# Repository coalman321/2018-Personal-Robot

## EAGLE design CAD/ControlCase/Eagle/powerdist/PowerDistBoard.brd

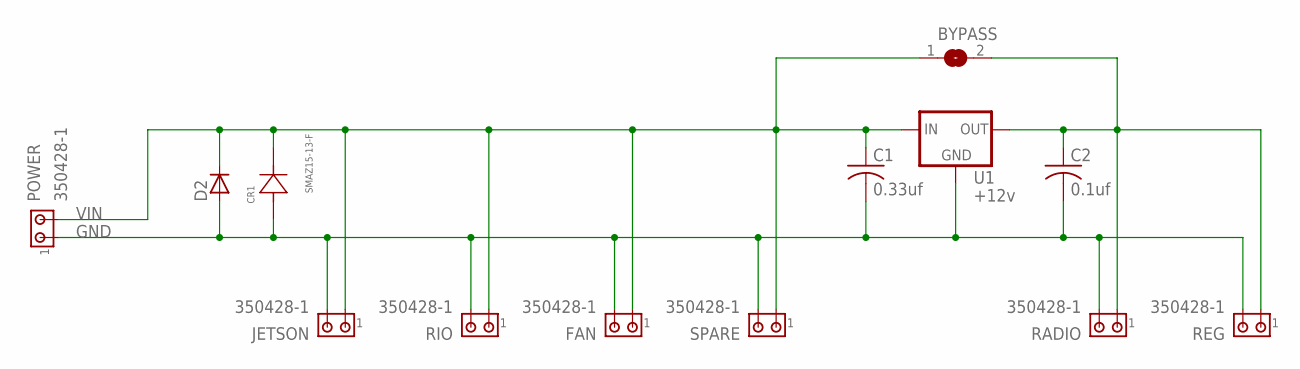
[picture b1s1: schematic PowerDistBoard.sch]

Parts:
BYPASS: SJW
C1: 0.33uf; C0603
C2: 0.1uf; C0603
CR1: SMAZ15-13-F; SMA
D2: D-SOD-80; SOD80
FAN: 350428-1
JETSON: 350428-1
POWER: 350428-1
RADIO: 350428-1
REG: 350428-1
RIO: 350428-1
SPARE: 350428-1
U1: +12v; TO-252

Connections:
GND: C1.2, C2.2, CR1.2 (21), D2.2 (A), FAN.2, JETSON.2, POWER.1, RADIO.2, REG.2, RIO.2, SPARE.2, U1.3 (GND)
unnamed: BYPASS.2, C2.1, RADIO.1, REG.1, U1.2 (OUT)
VIN: BYPASS.1, C1.1, CR1.1 (12), D2.1 (C), FAN.1, JETSON.1, POWER.2, RIO.1, SPARE.1, U1.1 (IN)

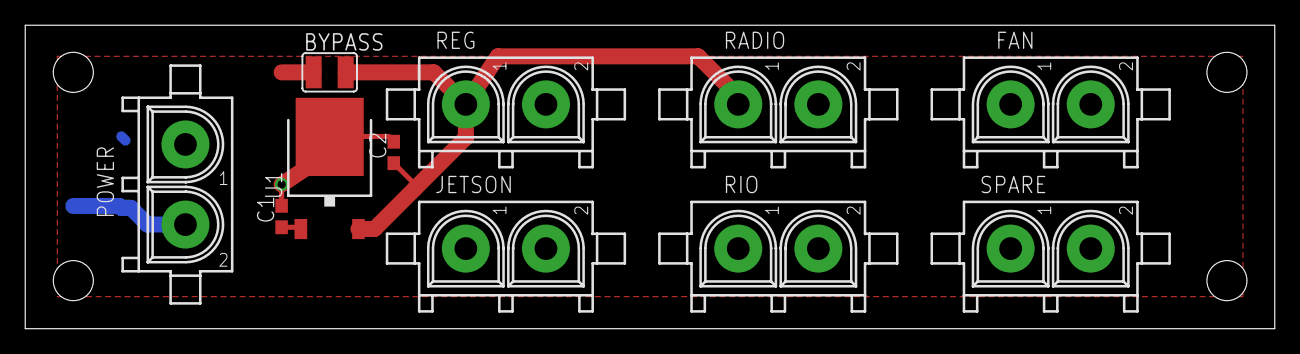
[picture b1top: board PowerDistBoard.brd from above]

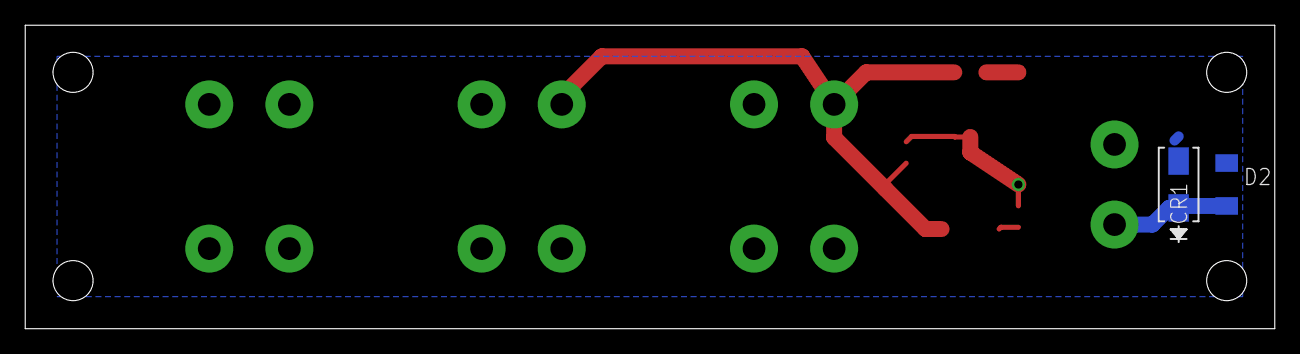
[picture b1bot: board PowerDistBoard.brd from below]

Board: 2 copper layers, 99.0 x 24.1 mm, 13 parts (2 on the bottom side), 3 nets.

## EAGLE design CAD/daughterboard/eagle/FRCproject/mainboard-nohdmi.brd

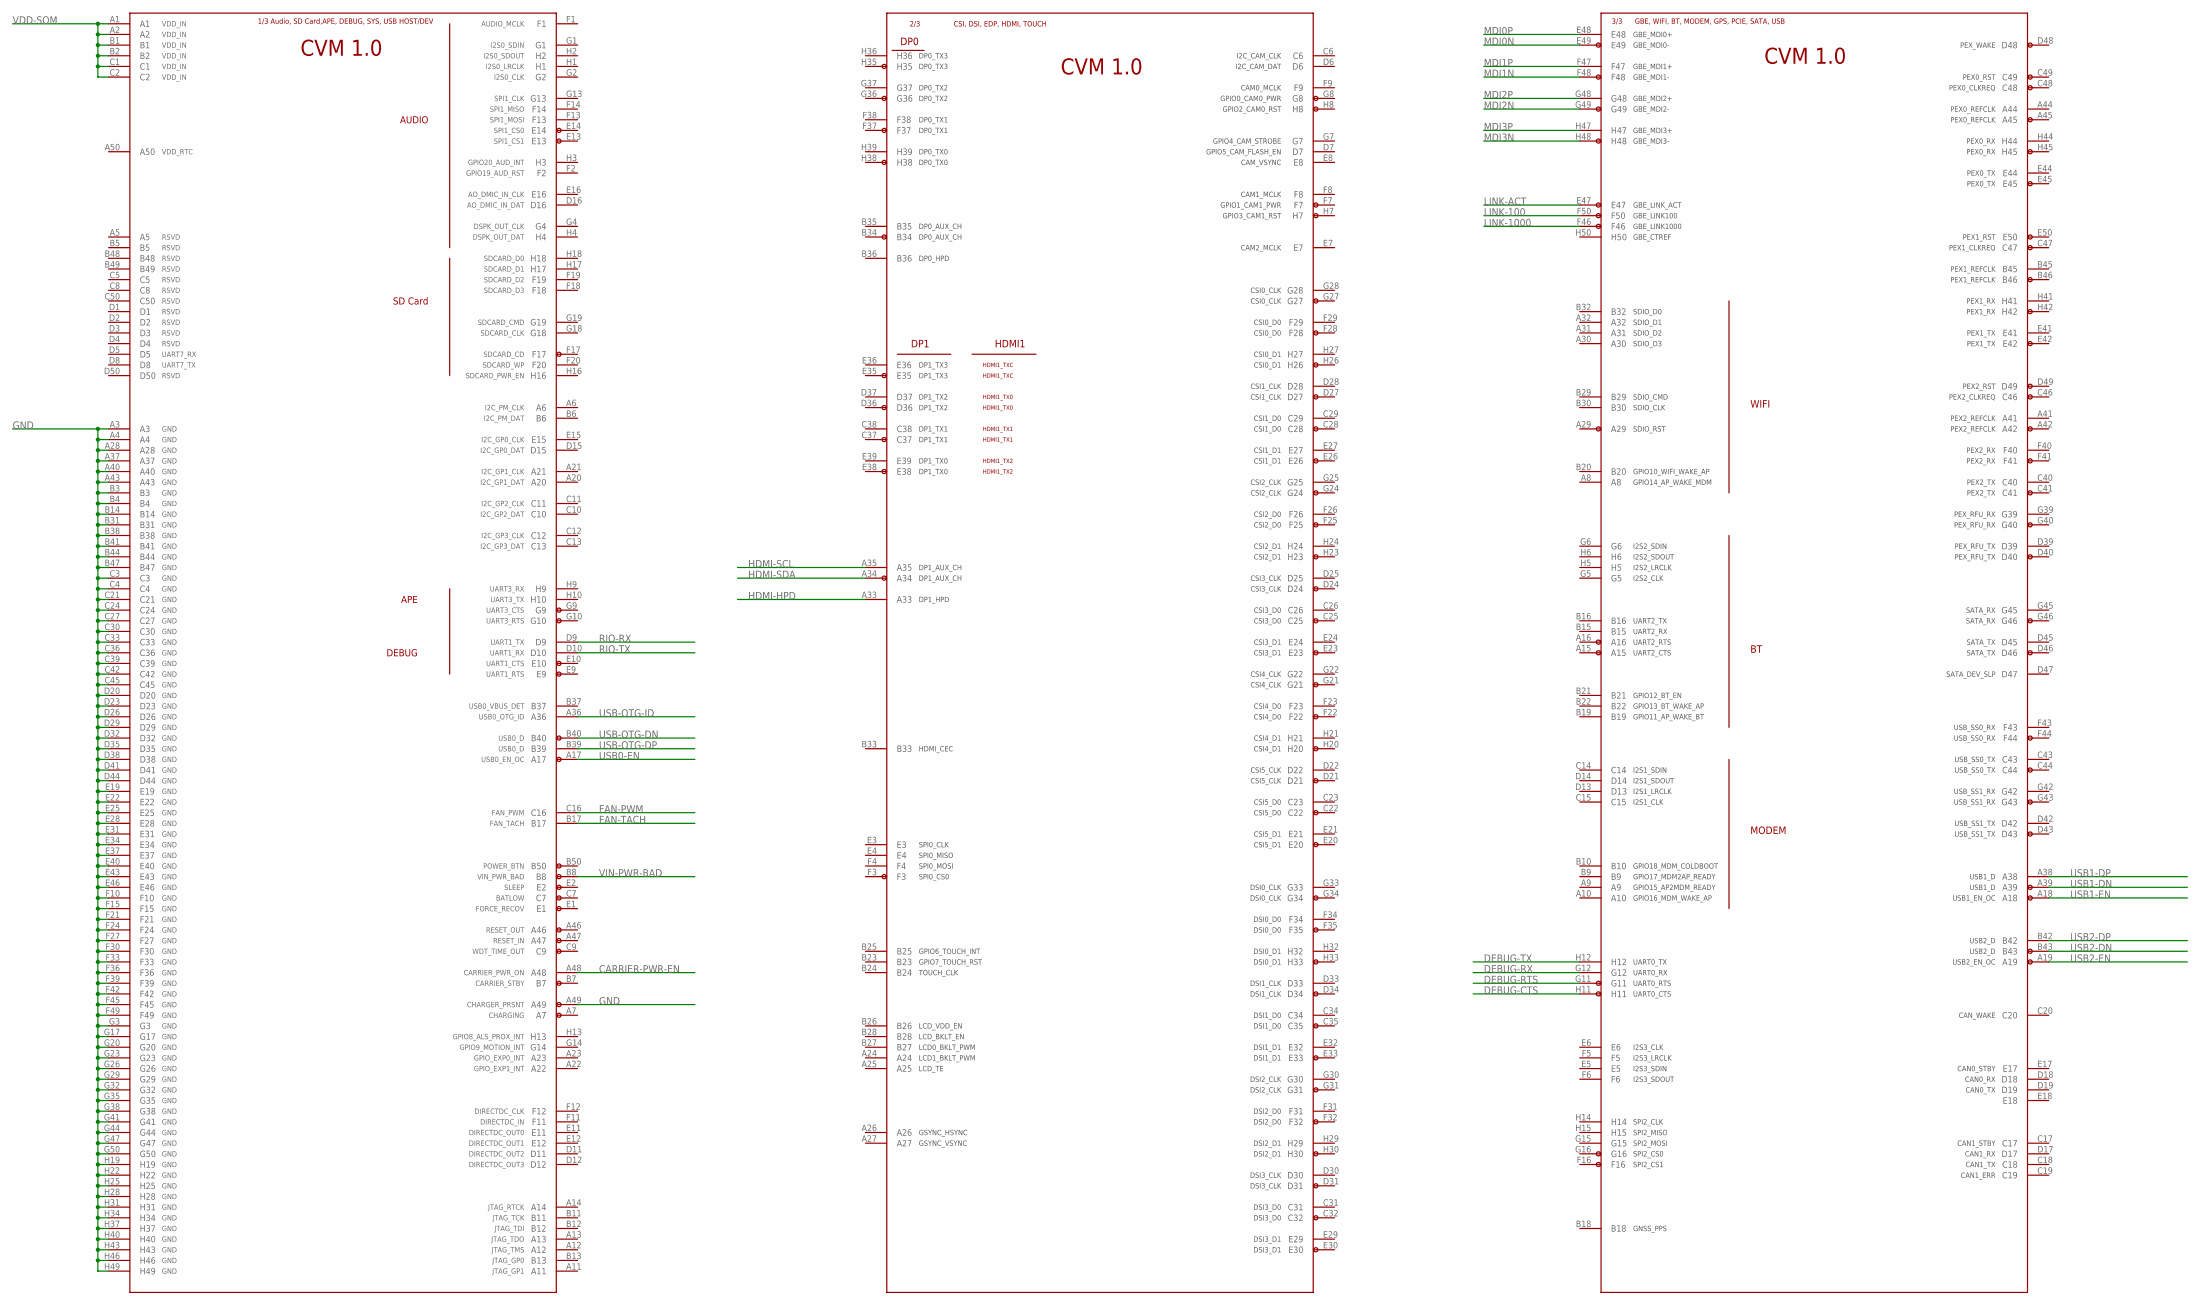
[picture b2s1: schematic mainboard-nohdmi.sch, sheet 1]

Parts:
U$1: JETSON-TX1; SEAM-50-02.0-L-08-2-A-K-TR

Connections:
CARRIER-PWR-EN: U$1.A48; also elsewhere on the board
DEBUG-CTS: U$1.H11
DEBUG-RTS: U$1.G11
DEBUG-RX: U$1.G12; also elsewhere on the board
DEBUG-TX: U$1.H12; also elsewhere on the board
FAN-PWM: U$1.C16
FAN-TACH: U$1.B17
GND: U$1.A3, U$1.A4, U$1.A28, U$1.A37, U$1.A40, U$1.A43, U$1.A49, U$1.B3, U$1.B4, U$1.B14, U$1.B31, U$1.B38, U$1.B41, U$1.B44, U$1.B47, U$1.C3, U$1.C4, U$1.C21, U$1.C24, U$1.C27, U$1.C30, U$1.C33, U$1.C36, U$1.C39, U$1.C42, U$1.C45, U$1.D20, U$1.D23, U$1.D26, U$1.D29, U$1.D32, U$1.D35, U$1.D38, U$1.D41, U$1.D44, U$1.E19, U$1.E22, U$1.E25, U$1.E28, U$1.E31, U$1.E34, U$1.E37, U$1.E40, U$1.E43, U$1.E46, U$1.F10, U$1.F15, U$1.F21, U$1.F24, U$1.F27, U$1.F30, U$1.F33, U$1.F36, U$1.F39, U$1.F42, U$1.F45, U$1.F49, U$1.G3, U$1.G17, U$1.G20, U$1.G23, U$1.G26, U$1.G29, U$1.G32, U$1.G35, U$1.G38, U$1.G41, U$1.G44, U$1.G47, U$1.G50, U$1.H19, U$1.H22, U$1.H25, U$1.H28, U$1.H31, U$1.H34, U$1.H37, U$1.H40, U$1.H43, U$1.H46, U$1.H49; also elsewhere on the board
HDMI-HPD: U$1.A33
HDMI-SCL: U$1.A35
HDMI-SDA: U$1.A34
LINK-100: U$1.F50; also elsewhere on the board
LINK-1000: U$1.F46
LINK-ACT: U$1.E47; also elsewhere on the board
MDI0N: U$1.E49; also elsewhere on the board
MDI0P: U$1.E48; also elsewhere on the board
MDI1N: U$1.F48; also elsewhere on the board
MDI1P: U$1.F47; also elsewhere on the board
MDI2N: U$1.G49; also elsewhere on the board
MDI2P: U$1.G48; also elsewhere on the board
MDI3N: U$1.H48; also elsewhere on the board
MDI3P: U$1.H47; also elsewhere on the board
RIO-RX: U$1.D9; also elsewhere on the board
RIO-TX: U$1.D10; also elsewhere on the board
USB0-EN: U$1.A17; also elsewhere on the board
USB1-DN: U$1.A39; also elsewhere on the board
USB1-DP: U$1.A38; also elsewhere on the board
USB1-EN: U$1.A18; also elsewhere on the board
USB2-DN: U$1.B43; also elsewhere on the board
USB2-DP: U$1.B42; also elsewhere on the board
USB2-EN: U$1.A19; also elsewhere on the board
USB-OTG-DN: U$1.B40; also elsewhere on the board
USB-OTG-DP: U$1.B39; also elsewhere on the board
USB-OTG-ID: U$1.A36; also elsewhere on the board
VDD-SOM: U$1.A1, U$1.A2, U$1.B1, U$1.B2, U$1.C1, U$1.C2; also elsewhere on the board
VIN-PWR-BAD: U$1.B8; also elsewhere on the board

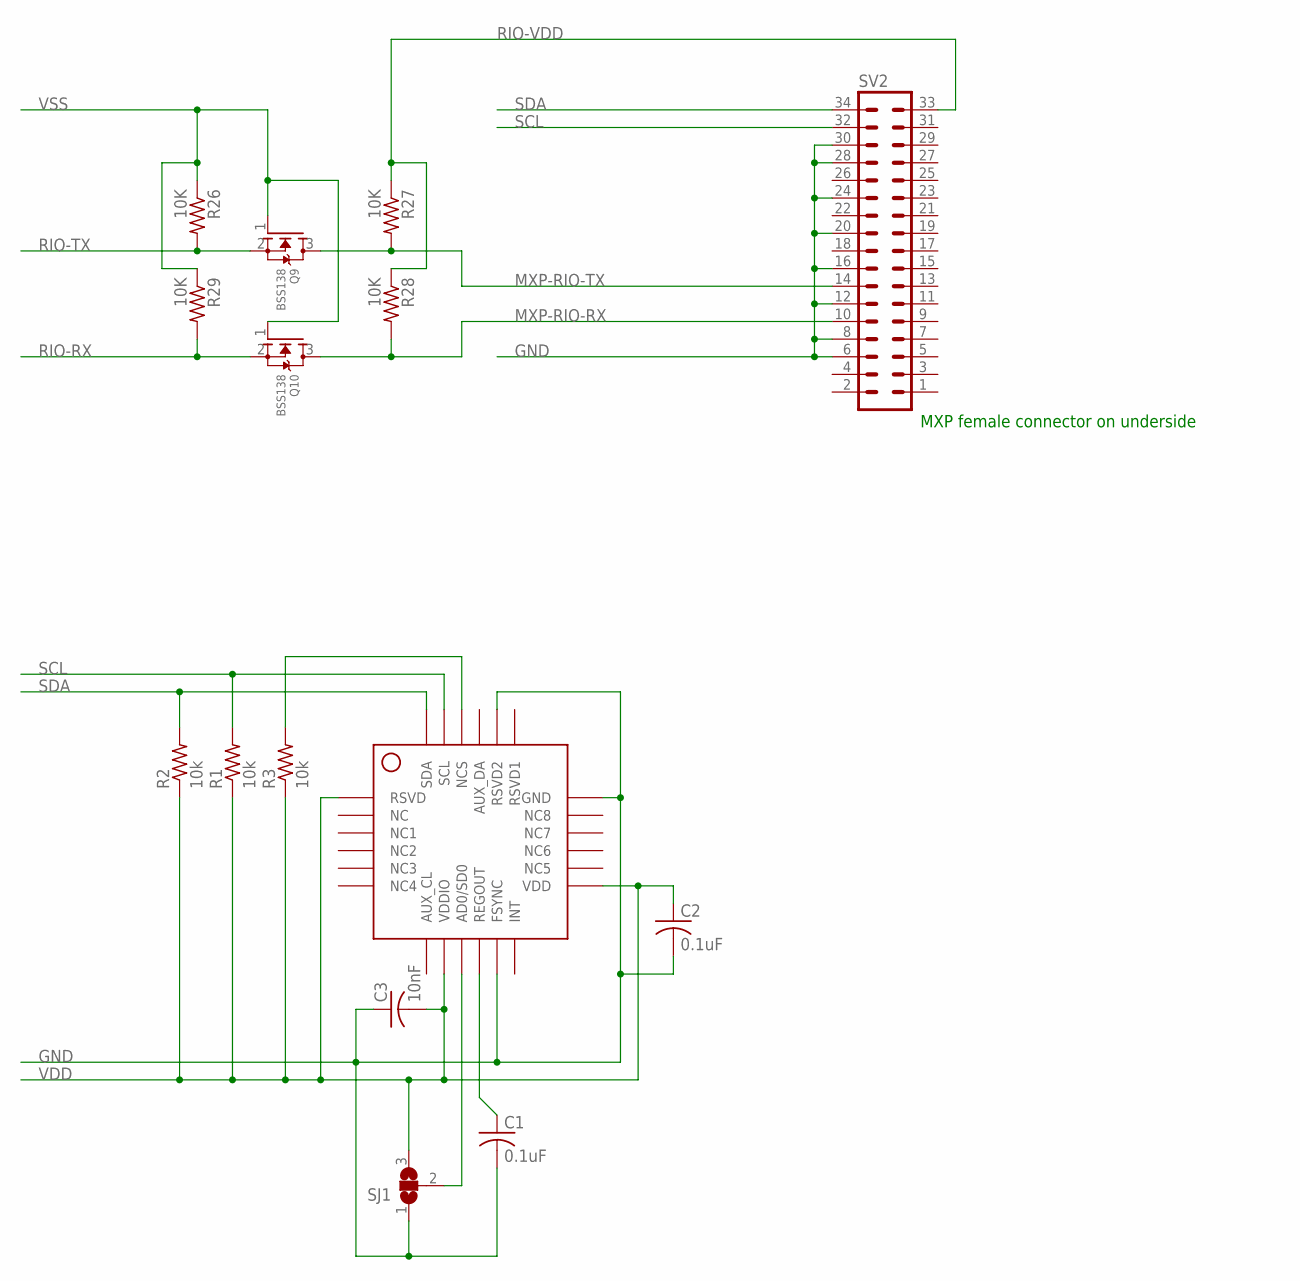
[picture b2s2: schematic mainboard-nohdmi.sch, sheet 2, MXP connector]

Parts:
C1, C2: 0.1uF; C0603
C3: 10nF; C0603
Q9, Q10: BSS138; SOT23
R1, R2, R3: 10k; R0603
R26, R27, R28, R29: 10K; R0603
SJ1: SJ2W; SJ_2
SV2: MA17-2
U$4: MPU9250; QFN3X3

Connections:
GND: C1.2, C2.2, C3.1, SJ1.1, SV2.6, SV2.8, SV2.12, SV2.16, SV2.20, SV2.24, SV2.28, SV2.30, U$4.P$11 (FSYNC), U$4.P$18 (GND), U$4.P$20 (RSVD2), U$4.P$25 (GND); also elsewhere on the board
MXP-RIO-RX: Q10.3 (D), R28.2, SV2.10
MXP-RIO-TX: Q9.3 (D), R27.2, SV2.14
unnamed: C1.1, U$4.P$10 (REGOUT)
unnamed: SJ1.2, U$4.P$9 (AD0/SD0)
unnamed: R3.2, U$4.P$22 (NCS)
RIO-RX: Q10.2 (S), R29.2; also elsewhere on the board
RIO-TX: Q9.2 (S), R26.2; also elsewhere on the board
RIO-VDD: R27.1, R28.1, SV2.33
SCL: R1.2, SV2.32, U$4.P$23 (SCL)
SDA: R2.2, SV2.34, U$4.P$24 (SDA)
VDD: C2.1, C3.2, R1.1, R2.1, R3.1, SJ1.3, U$4.P$1 (RSVD), U$4.P$8 (VDDIO), U$4.P$13 (VDD); also elsewhere on the board
VSS: Q9.1 (G), Q10.1 (G), R26.1, R29.1; also elsewhere on the board

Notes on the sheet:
MXP female connector on underside

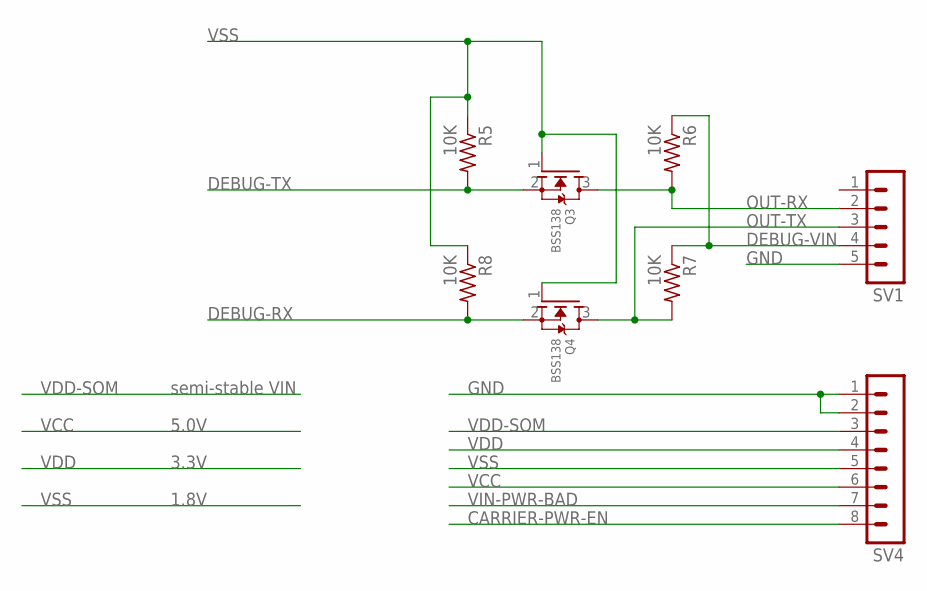
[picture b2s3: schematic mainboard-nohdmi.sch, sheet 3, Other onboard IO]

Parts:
Q3, Q4: BSS138; SOT23
R5, R6, R7, R8: 10K; R0603
SV1: MA05-1
SV4: MA08-1

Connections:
CARRIER-PWR-EN: SV4.8; also elsewhere on the board
DEBUG-RX: Q4.2 (S), R8.2; also elsewhere on the board
DEBUG-TX: Q3.2 (S), R5.2; also elsewhere on the board
DEBUG-VIN: R6.1, R7.1, SV1.4
GND: SV1.5, SV4.1, SV4.2; also elsewhere on the board
OUT-RX: Q3.3 (D), R6.2, SV1.2
OUT-TX: Q4.3 (D), R7.2, SV1.3
VCC: SV4.6; also elsewhere on the board
VDD: SV4.4; also elsewhere on the board
VDD-SOM: SV4.3; also elsewhere on the board
VIN-PWR-BAD: SV4.7; also elsewhere on the board
VSS: Q3.1 (G), Q4.1 (G), R5.1, R8.1, SV4.5; also elsewhere on the board

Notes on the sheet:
semi-stable VIN
5.0V
3.3V
1.8V

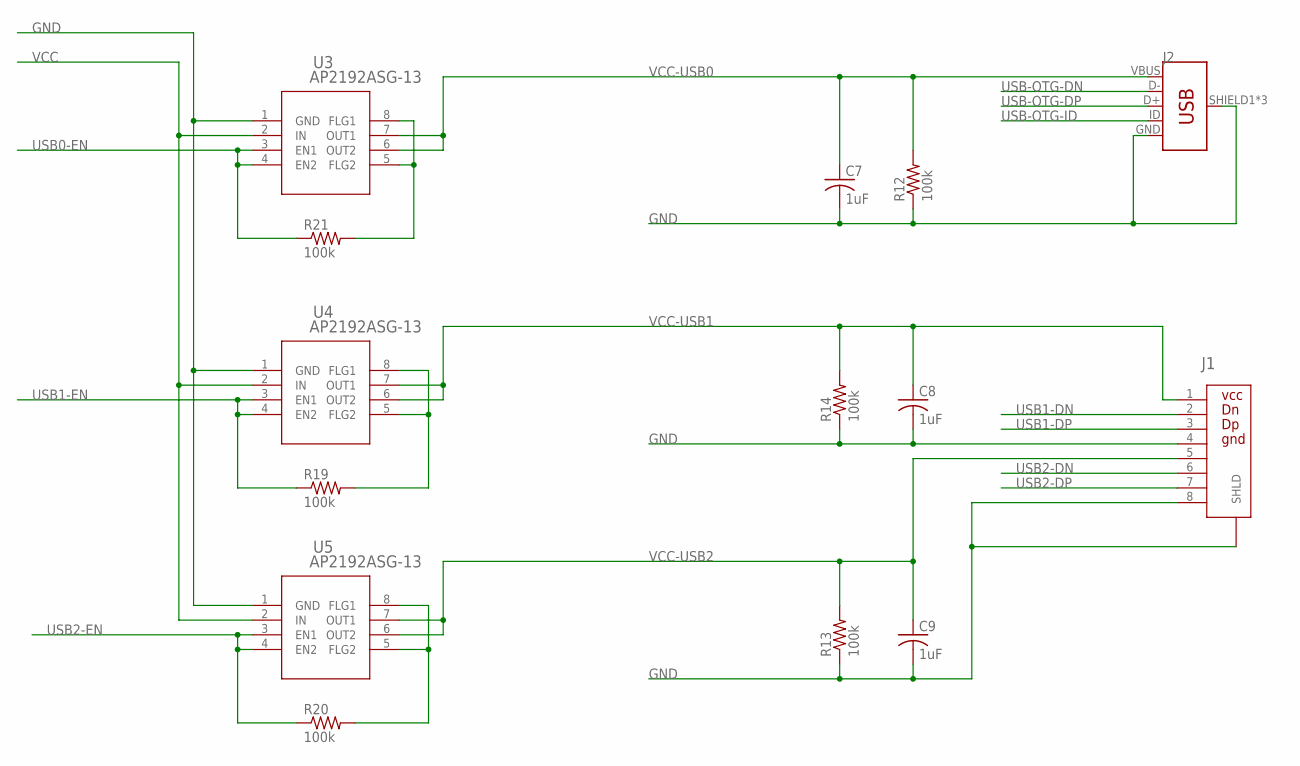
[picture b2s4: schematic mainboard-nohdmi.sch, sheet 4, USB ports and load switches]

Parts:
C7, C8, C9: 1uF; C0805
J1: 1903815-1; CONN_1903815-1
J2: USB_MICRO-B_FEMALE-SMT; USB-B-MICRO-SMD
R12, R13, R14, R19, R20, R21: 100k; R0603
U3, U4, U5: AP2192ASG-13; SO8

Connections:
GND: C7.2, C8.2, C9.2, J1.4, J1.8, J1.SHLD1 (SHLD), J1.SHLD2 (SHLD), J1.SHLD3 (SHLD), J1.SHLD4 (SHLD), J2.GND, J2.SHIELD1 (SHIELD), J2.SHIELD2 (SHIELD), J2.SHIELD3 (SHIELD), R12.1, R13.1, R14.1, U3.1 (GND), U4.1 (GND), U5.1 (GND); also elsewhere on the board
unnamed: R20.2, U5.5 (FLG2), U5.8 (FLG1)
unnamed: R19.2, U4.5 (FLG2), U4.8 (FLG1)
unnamed: R21.2, U3.5 (FLG2), U3.8 (FLG1)
USB0-EN: R21.1, U3.3 (EN1), U3.4 (EN2); also elsewhere on the board
USB1-DN: J1.2; also elsewhere on the board
USB1-DP: J1.3; also elsewhere on the board
USB1-EN: R19.1, U4.3 (EN1), U4.4 (EN2); also elsewhere on the board
USB2-DN: J1.6; also elsewhere on the board
USB2-DP: J1.7; also elsewhere on the board
USB2-EN: R20.1, U5.3 (EN1), U5.4 (EN2); also elsewhere on the board
USB-OTG-DN: J2.D-; also elsewhere on the board
USB-OTG-DP: J2.D+; also elsewhere on the board
USB-OTG-ID: J2.ID; also elsewhere on the board
VCC: U3.2 (IN), U4.2 (IN), U5.2 (IN); also elsewhere on the board
VCC-USB0: C7.1, J2.VBUS, R12.2, U3.6 (OUT2), U3.7 (OUT1)
VCC-USB1: C8.1, J1.1, R14.2, U4.6 (OUT2), U4.7 (OUT1)
VCC-USB2: C9.1, J1.5, R13.2, U5.6 (OUT2), U5.7 (OUT1)

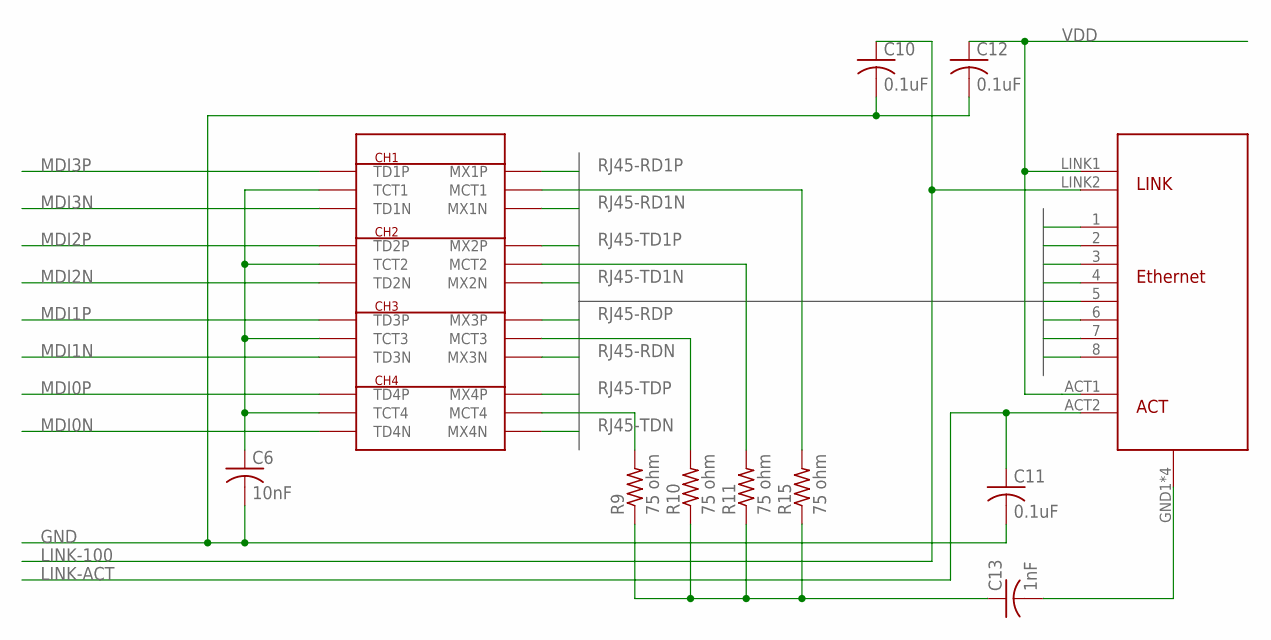
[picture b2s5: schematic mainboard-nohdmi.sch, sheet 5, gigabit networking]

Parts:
C6: 10nF; C0805
C10, C11, C12: 0.1uF; C0805
C13: 1nF; C0805
R9, R10, R11, R15: 75 ohm; R0603
U$3: 2-406549-1
U$5: H6062NL; H60XXNL

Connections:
GND: C6.2, C10.2, C11.2, C12.2; also elsewhere on the board
LINK-100: C10.1, U$3.LINK2; also elsewhere on the board
LINK-ACT: C11.1, U$3.ACT2; also elsewhere on the board
MDI0N: U$5.P$24 (TD4N); also elsewhere on the board
MDI0P: U$5.P$22 (TD4P); also elsewhere on the board
MDI1N: U$5.P$21 (TD3N); also elsewhere on the board
MDI1P: U$5.P$19 (TD3P); also elsewhere on the board
MDI2N: U$5.P$18 (TD2N); also elsewhere on the board
MDI2P: U$5.P$16 (TD2P); also elsewhere on the board
MDI3N: U$5.P$15 (TD1N); also elsewhere on the board
MDI3P: U$5.P$13 (TD1P); also elsewhere on the board
unnamed: C13.2, U$3.GND1, U$3.GND2, U$3.GND3, U$3.GND4
unnamed: R9.2, U$5.P$11 (MCT4)
unnamed: R10.2, U$5.P$8 (MCT3)
unnamed: R11.2, U$5.P$5 (MCT2)
unnamed: R15.2, U$5.P$2 (MCT1)
unnamed: C13.1, R9.1, R10.1, R11.1, R15.1
unnamed: C6.1, U$5.P$14 (TCT1), U$5.P$17 (TCT2), U$5.P$20 (TCT3), U$5.P$23 (TCT4)
RJ45-RD1N: U$3.8, U$5.P$3 (MX1N)
RJ45-RD1P: U$3.7, U$5.P$1 (MX1P)
RJ45-RDN: U$3.6, U$5.P$9 (MX3N)
RJ45-RDP: U$3.3, U$5.P$7 (MX3P)
RJ45-TD1N: U$3.5, U$5.P$6 (MX2N)
RJ45-TD1P: U$3.4, U$5.P$4 (MX2P)
RJ45-TDN: U$3.2, U$5.P$12 (MX4N)
RJ45-TDP: U$3.1, U$5.P$10 (MX4P)
VDD: C12.1, U$3.ACT1, U$3.LINK1; also elsewhere on the board

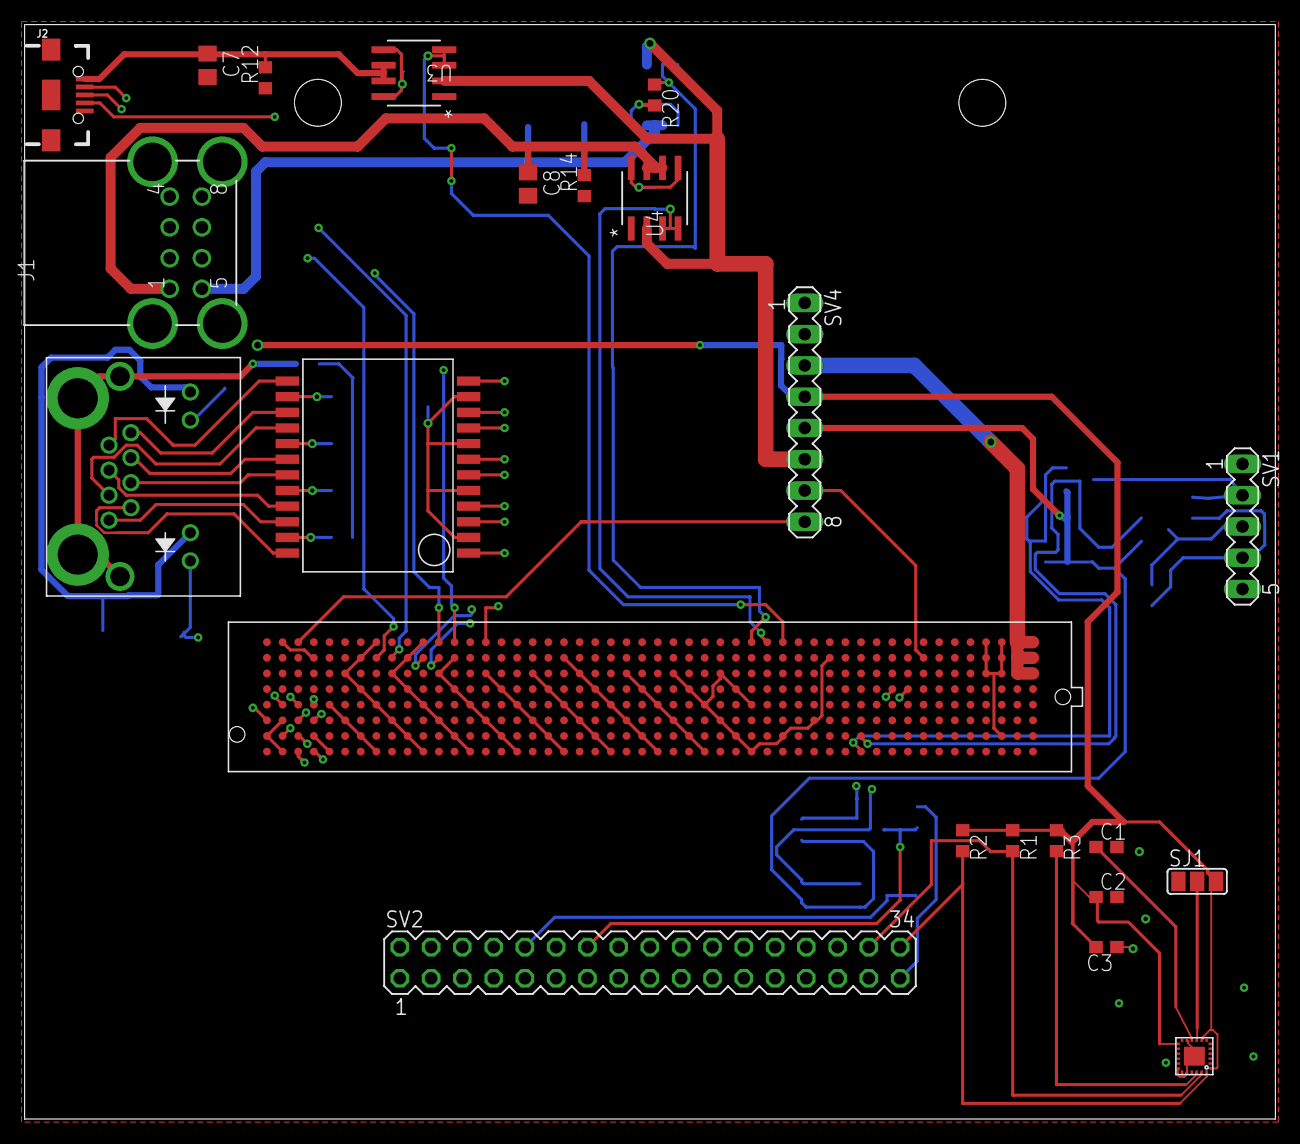
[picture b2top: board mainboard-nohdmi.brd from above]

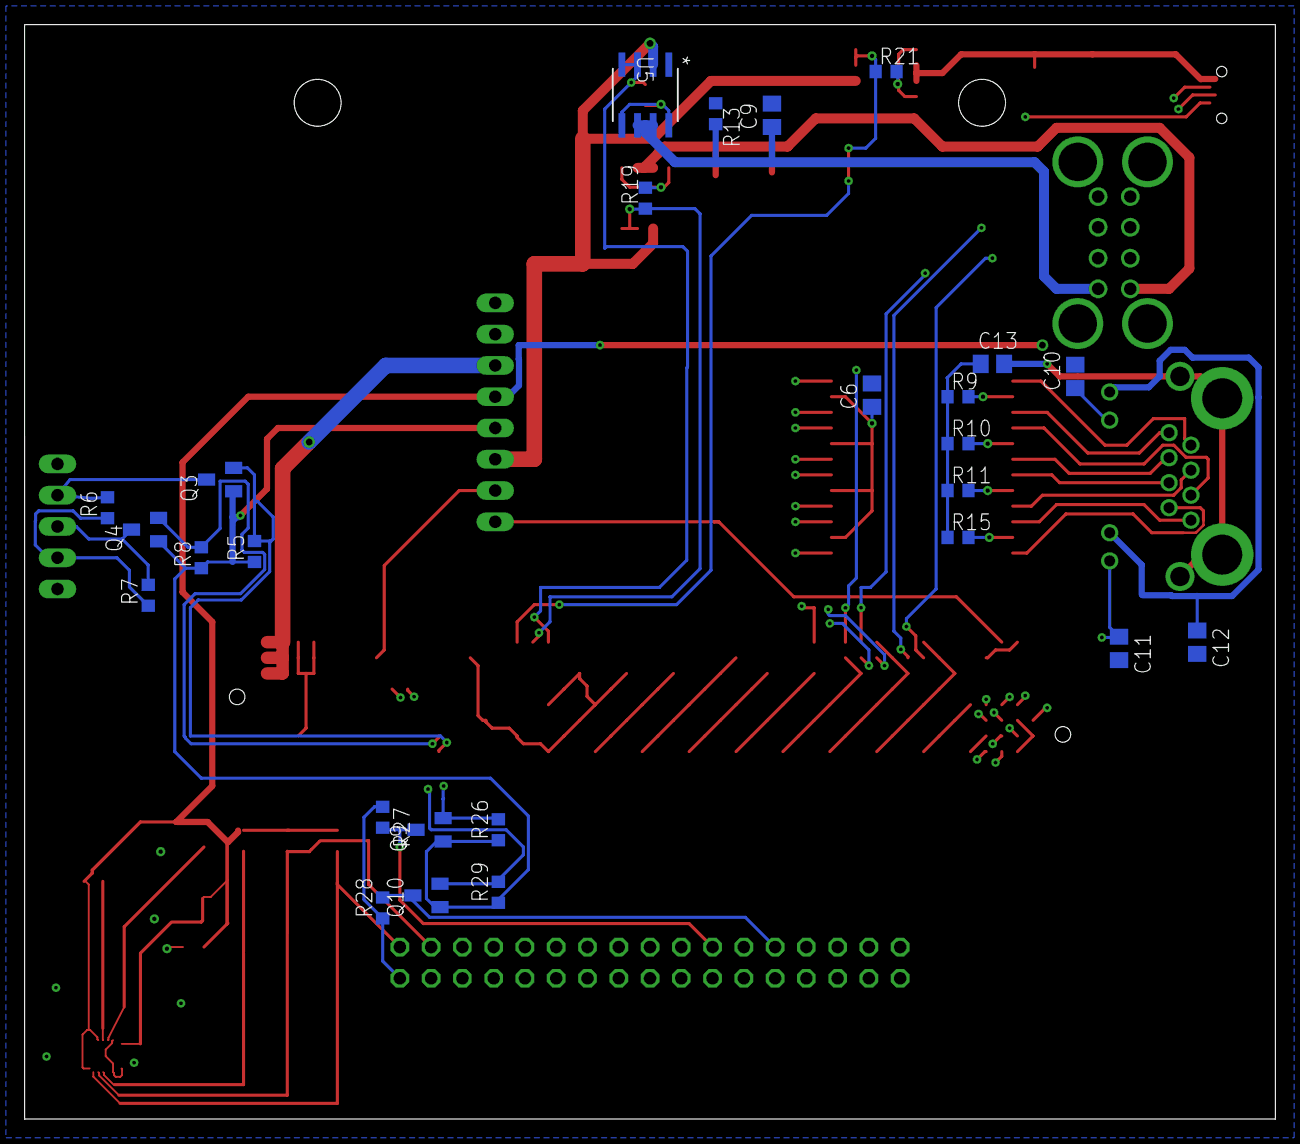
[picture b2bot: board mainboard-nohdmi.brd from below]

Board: 6 copper layers, 101.6 x 88.9 mm, 49 parts (26 on the bottom side), 63 nets.

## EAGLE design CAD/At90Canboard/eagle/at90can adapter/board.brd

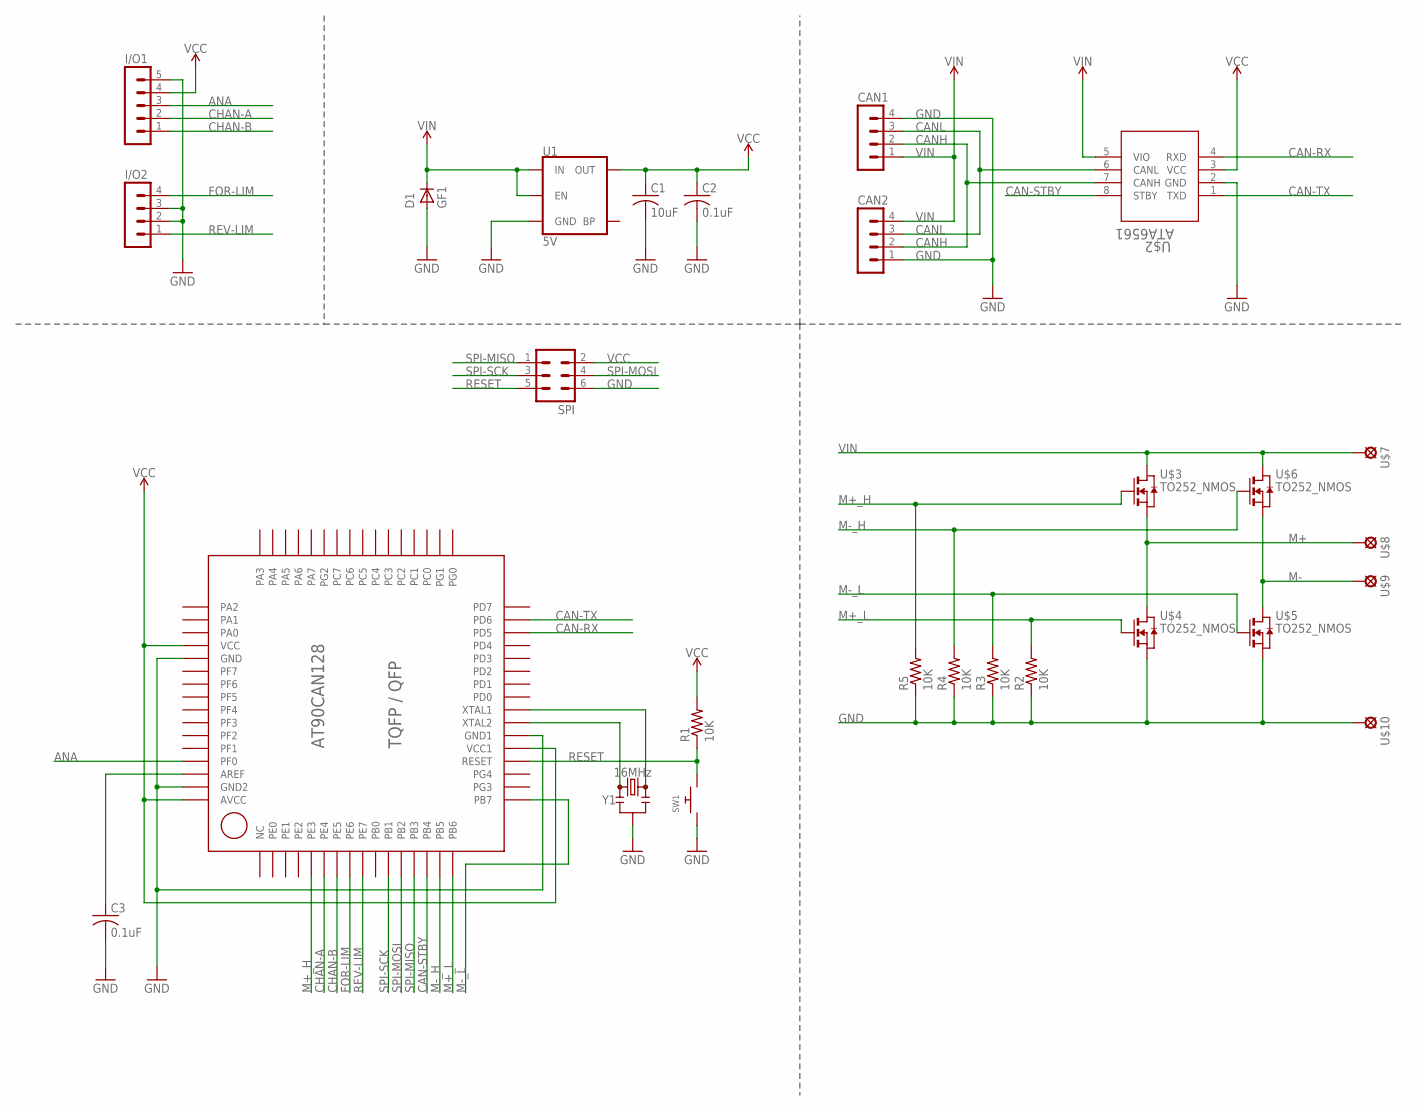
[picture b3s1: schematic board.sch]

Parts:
C1: 10uF; C0603
C2, C3: 0.1uF; C0603
CAN1, CAN2: MA04-1
D1: GF1; SMA-DO214AC
I/O1: MA05-1
I/O2: MA04-1
R1, R2, R3, R4, R5: 10K; R0603
SPI: MA03-2
SW1: SWITCH_PUSHBUTTONEVQ-PE; TACT_PANA-EVQ
U1: 5V; SOT23-5
U$1: AT90CAN128; QFP64/TQFP64
U$2: ATA6561; SO8
U$3, U$4, U$5, U$6: TO252_NMOS; TO252
U$7, U$8, U$9, U$10: SOLPAD
Y1: 16MHz; RESONATOR-SMD-3.2X1.3

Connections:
ANA: I/O1.3, U$1.61 (PF0)
CAN-RX: U$1.30 (PD5), U$2.4 (RXD)
CAN-STBY: U$1.14 (PB4), U$2.8 (STBY)
CAN-TX: U$1.31 (PD6), U$2.1 (TXD)
CANH: CAN1.2, CAN2.2, U$2.7 (CANH)
CANL: CAN1.3, CAN2.3, U$2.6 (CANL)
CHAN-A: I/O1.2, U$1.6 (PE4)
CHAN-B: I/O1.1, U$1.7 (PE5)
FOR-LIM: I/O2.4, U$1.8 (PE6)
GND: C1.2, C2.2, C3.2, CAN1.4, CAN2.1, D1.A, I/O1.5, I/O2.2, I/O2.3, R2.1, R3.1, R4.1, R5.1, SPI.6, SW1.P$1, U1.2 (GND), U$1.22 (GND1), U$1.53 (GND), U$1.63 (GND2), U$2.2 (GND), U$4.2 (S), U$5.2 (S), U$10.P$1, Y1.2
M+: U$3.2 (S), U$4.3 (D), U$8.P$1
M+_H: R5.2, U$1.5 (PE3), U$3.1 (G)
M+_L: R2.2, U$1.16 (PB6), U$4.1 (G)
M-: U$5.3 (D), U$6.2 (S), U$9.P$1
M-_H: R4.2, U$1.15 (PB5), U$6.1 (G)
M-_L: R3.2, U$1.17 (PB7), U$5.1 (G)
unnamed: U$1.23 (XTAL2), Y1.1
unnamed: U$1.24 (XTAL1), Y1.3
unnamed: C3.1, U$1.62 (AREF)
RESET: R1.1, SPI.5, SW1.P$2, U$1.20 (RESET)
REV-LIM: I/O2.1, U$1.9 (PE7)
SPI-MISO: SPI.1, U$1.13 (PB3)
SPI-MOSI: SPI.4, U$1.12 (PB2)
SPI-SCK: SPI.3, U$1.11 (PB1)
VCC: C1.1, C2.1, I/O1.4, R1.2, SPI.2, U1.5 (OUT), U$1.21 (VCC1), U$1.52 (VCC), U$1.64 (AVCC), U$2.3 (VCC)
VIN: CAN1.1, CAN2.4, D1.K (C), U1.1 (IN), U1.3 (EN), U$2.5 (VIO), U$3.3 (D), U$6.3 (D), U$7.P$1

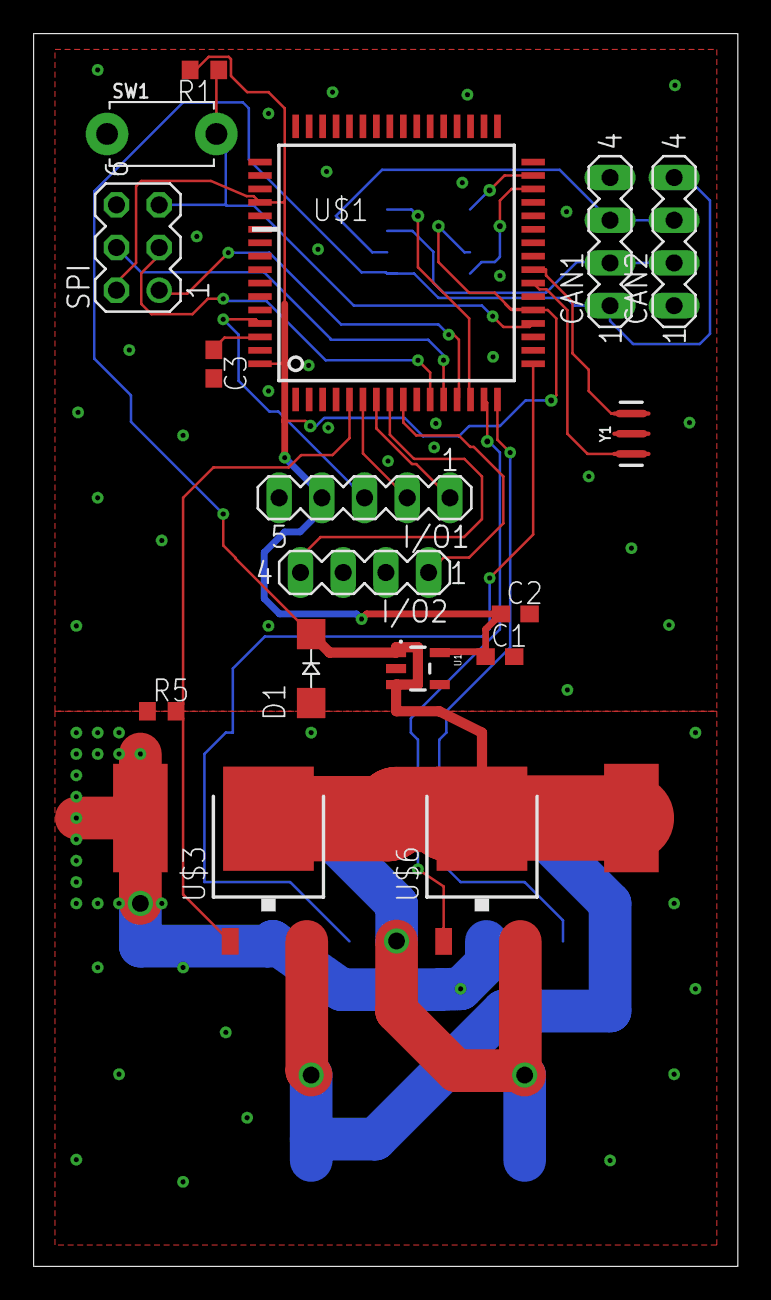
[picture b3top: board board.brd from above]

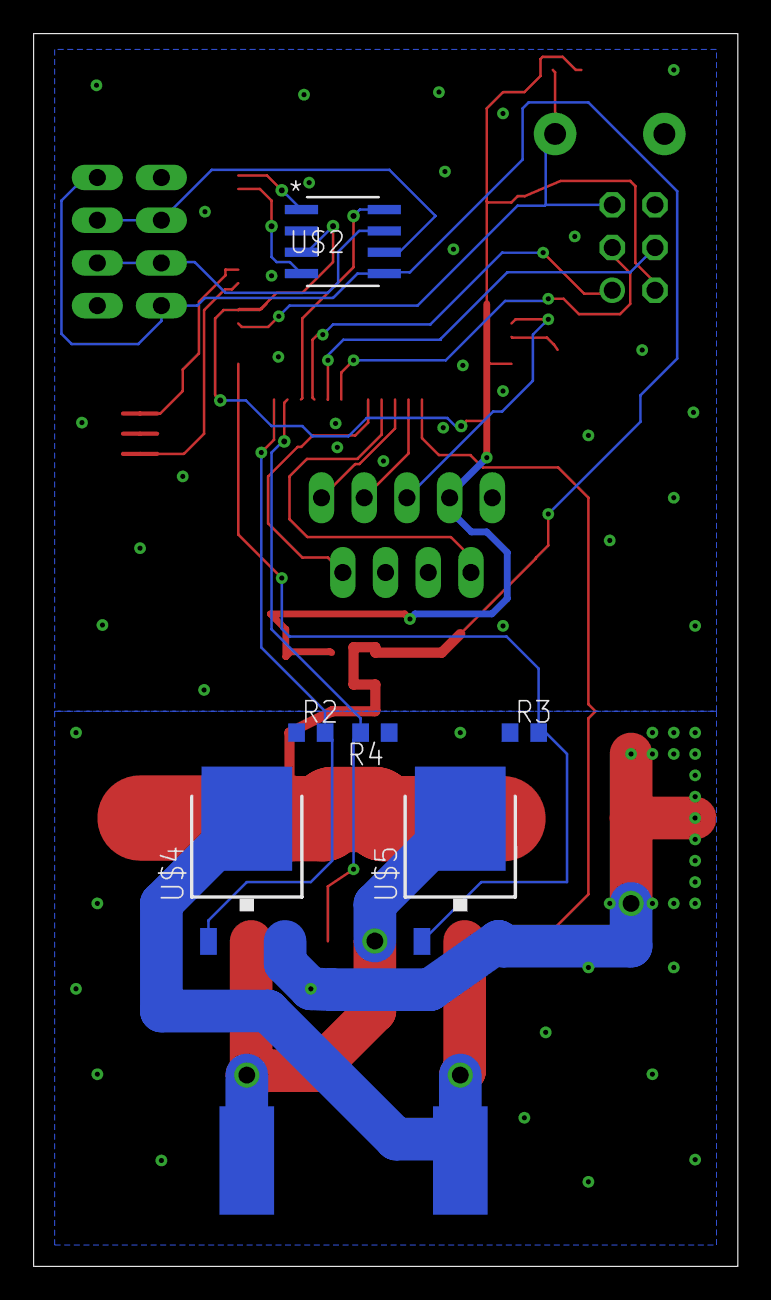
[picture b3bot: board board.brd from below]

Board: 2 copper layers, 41.9 x 73.3 mm, 27 parts (8 on the bottom side), 26 nets.

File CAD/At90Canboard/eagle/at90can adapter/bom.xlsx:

Part | Value | Device | Package | Description | MF | MPN | OC_FARNELL | OC_NEWARK | PROD_ID
C1 | 10uF | C-USC0603 | C0603 | CAPACITOR, American symbol
C2 | 0.1uF | C-USC0603 | C0603 | CAPACITOR, American symbol
C3 | 0.1uF | C-USC0603 | C0603 | CAPACITOR, American symbol
CAN1 | N/A | MA04-1 | MA04-1 | PIN HEADER |  |  | unknown | unknown
CAN2 | N/A | MA04-1 | MA04-1 | PIN HEADER |  |  | unknown | unknown
D1 | GF1 | GF1 | SMA-DO214AC | DIODE
I/O1 | N/A | MA05-1 | MA05-1 | PIN HEADER |  |  | unknown | unknown
I/O2 | N/A | MA04-1 | MA04-1 | PIN HEADER |  |  | unknown | unknown
R1 | 10K | R-US_R0603 | R0603 | RESISTOR, American symbol
R2 | 10K | R-US_R0603 | R0603 | RESISTOR, American symbol
R3 | 10K | R-US_R0603 | R0603 | RESISTOR, American symbol
R4 | 10K | R-US_R0603 | R0603 | RESISTOR, American symbol
R5 | 10K | R-US_R0603 | R0603 | RESISTOR, American symbol
SPI | N/A | MA03-2 | MA03-2 | PIN HEADER |  |  | unknown | unknown
SW1 | N/A | SWITCH_PUSHBUTTONEVQ-PE | TACT_PANA-EVQ | Buttons
U$1 | AT90CAN128 | AT90CAN128 | QFP64/TQFP64 | N/A
U$2 | ATA6561 | ATA6561 | SO8 | N/A
U$3 | TO252_NMOS | TO252_NMOS | TO252 | N/A
U$4 | TO252_NMOS | TO252_NMOS | TO252 | N/A
U$5 | TO252_NMOS | TO252_NMOS | TO252 | N/A
U$6 | TO252_NMOS | TO252_NMOS | TO252 | N/A
U1 | 5V | V_REG_MIC5205_5V | SOT23-5 | V_REG MIC5205 Standard 3.3V, 5V, and Adjustable 150mA LDO voltage regulator in 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 |  |  |  |  | VREG-00823
Y1 | 16MHz | RESONATOR-16MHZSMD_3.2X1.3 | RESONATOR-SMD-3.2X1.3 | 16MHz Resonator |  |  |  |  | XTAL-08900

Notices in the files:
parts and their libraries:
SparkFun-IC-Power: Licensing: Creative Commons ShareAlike 4.0 International - https://creativecommons.org/licenses/by-sa/4.0
